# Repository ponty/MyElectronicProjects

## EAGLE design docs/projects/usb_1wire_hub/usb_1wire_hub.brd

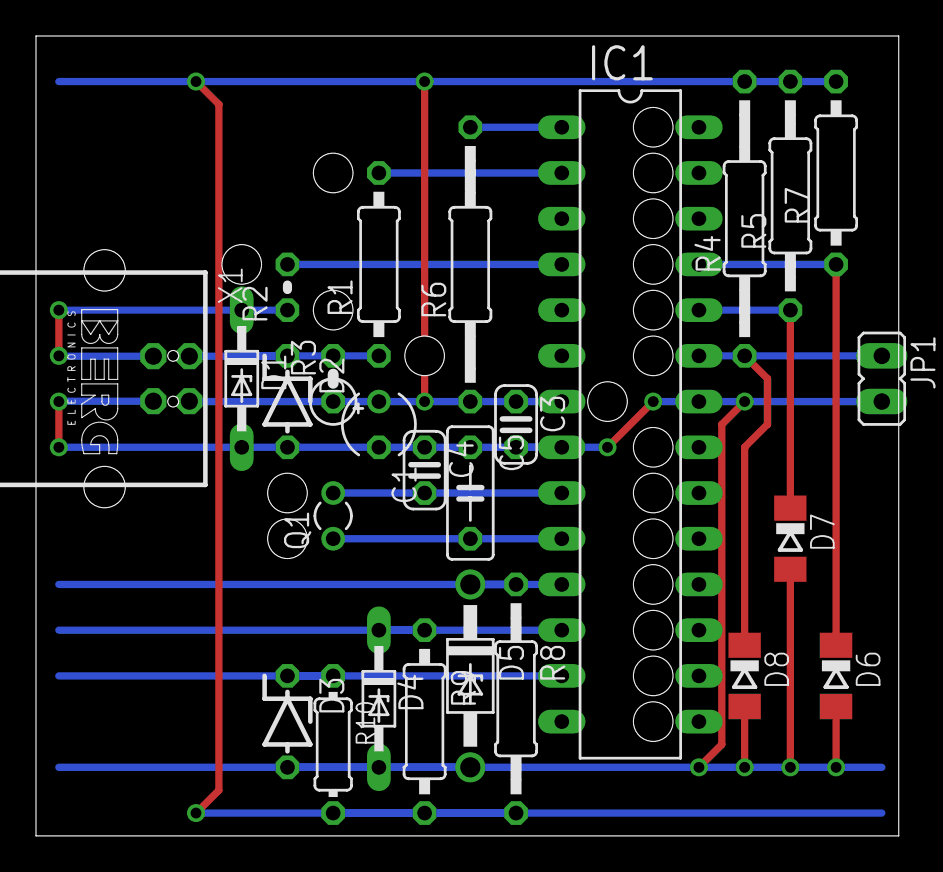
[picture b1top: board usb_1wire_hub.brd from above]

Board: 2 copper layers, 47.9 x 44.4 mm, 26 parts (0 on the bottom side), 15 nets.

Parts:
C1: 4u7; TT2D4
C3: 100n; C025-024X044
C4: 22p; C025-024X044
C5: 22p; C050-025X075
D1: 3V6; DO34Z7
D2: 3V6; ZDIO-5
D3: 5V1; ZDIO-5
D4: 5V1; DO34Z7
D5: 5V1; DO41Z10
D6, D7, D8: 5V1; SOD80C
IC1: DIL28-3
JP1: JP1
Q1: 12MHz; TC26V
R1: 68; 0207/10
R2: 68; 0204V
R3: 2k2; 0207/2V
R4: 4k7; 0207/15
R5, R8: 4k7; 0207/12
R6: 10k; 0207/15
R7, R9: 4k7; 0207/10
R10: 4k7; 0204/7
X1: PN61729

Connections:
+5V: C1.+, C3.1, IC1.7, R3.1, R4.2, R5.2, R6.1, R7.2, R8.2, R9.2, R10.2, X1.1
D+: D1.C, R2.1, X1.3
D-: D2.C, R1.1, R3.2, X1.2
GND: C1.-, C3.2, C4.1, C5.1, D1.A, D2.A, D3.A, D4.A, D5.A, D6.A, D7.A, D8.A, IC1.8, IC1.22, JP1.2, X1.4
unnamed: IC1.1, R6.2
unnamed: IC1.2, R1.2
unnamed: IC1.4, R2.2
unnamed: D8.C, IC1.23, JP1.1, R4.1
unnamed: D3.C, IC1.13, R10.1
unnamed: D7.C, IC1.24, R5.1
unnamed: D6.C, IC1.25, R7.1
unnamed: D4.C, IC1.12, R9.1
unnamed: D5.C, IC1.11, R8.1
unnamed: C4.2, IC1.9, Q1.2
unnamed: C5.2, IC1.10, Q1.1
